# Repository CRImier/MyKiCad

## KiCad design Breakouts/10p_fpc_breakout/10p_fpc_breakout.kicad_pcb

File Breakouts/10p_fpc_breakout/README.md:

# 10-pin FPC/FFC breakout - 0.5/0.8/1mm

This is a simple breakout that exposes all pins of a 10-pin FFC connector.
You can do whatever with it.

On one side, there's footprints for 0.5mm and 0.8mm connectors.
On the other side, there's a footprint for 1mm connectors.

For instance, it should be quite usable for Sharp memory LCDs.
It will kinda sorta work for smaller-pin-count connectors too.

## Notes

- Pin headers are arranged in a way that this board can be plugged into a breadboard.

## Info

- Software: Kicad 6
- Version: 1
- PCB size: 9*20mm
- Layer count: 2

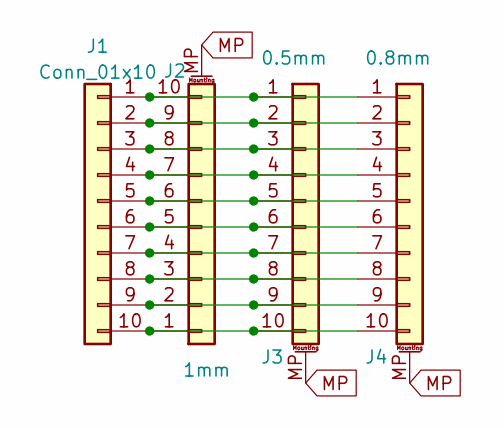
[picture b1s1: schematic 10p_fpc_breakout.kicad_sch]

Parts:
J1: Conn_01x10; PinHeader_1x10_P2.00mm_Vertical
J2: 1mm; FPC_10_10
J3: 0.5mm; FPC_10_05
J4: 0.8mm; FPC_10_08

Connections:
MP: J2.MP (MountPin), J3.MP (MountPin), J4.MP (MountPin)
unnamed: J1.1, J2.10, J3.1, J4.1
unnamed: J1.2, J2.9, J3.2, J4.2
unnamed: J1.3, J2.8, J3.3, J4.3
unnamed: J1.4, J2.7, J3.4, J4.4
unnamed: J1.5, J2.6, J3.5, J4.5
unnamed: J1.6, J2.5, J3.6, J4.6
unnamed: J1.7, J2.4, J3.7, J4.7
unnamed: J1.8, J2.3, J3.8, J4.8
unnamed: J1.9, J2.2, J3.9, J4.9
unnamed: J1.10, J2.1, J3.10, J4.10

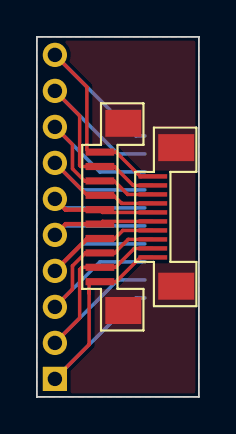
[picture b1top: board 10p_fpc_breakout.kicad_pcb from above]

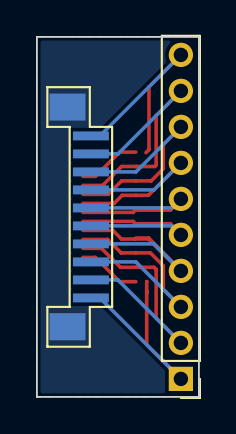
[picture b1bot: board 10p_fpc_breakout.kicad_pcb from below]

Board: 2 copper layers, 9.0 x 20.0 mm, 4 parts (2 on the bottom side), 11 nets.

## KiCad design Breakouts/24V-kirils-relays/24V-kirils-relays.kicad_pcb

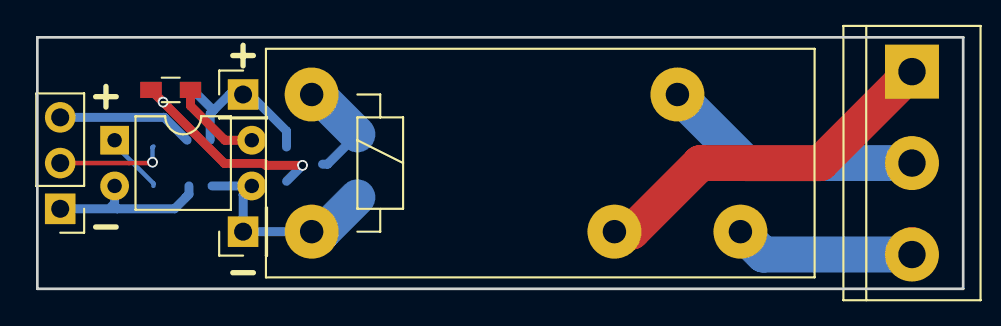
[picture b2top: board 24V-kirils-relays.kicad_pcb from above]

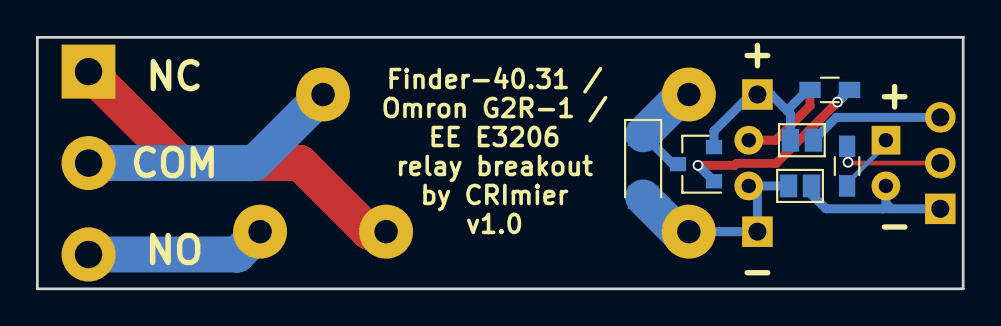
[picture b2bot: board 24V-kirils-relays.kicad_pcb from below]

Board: 2 copper layers, 51.4 x 14.0 mm, 13 parts (6 on the bottom side), 12 nets.

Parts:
D1: D_Small; D_MiniMELF
J1: Conn_01x03; Pin_Header_Straight_1x03_Pitch2.54mm
J2, J4: Conn_01x01; Pin_Header_Straight_1x01_Pitch2.54mm
J3: Conn_01x03; TerminalBlock_bornier-3_P5.08mm
JP1, JP2: Jumper; GS2
K1: FINDER-40.31; Relay_SPDT_Finder_40.31
Q1: Q_PNP_BEC; SOT-23
R1, R2, R3: 1k; R_0603_HandSoldering
U1: PC817; DIP-4_W7.62mm

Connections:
GND: J1.1, JP2.1, U1.2
unnamed: D1.1, K1.A1, Q1.3
unnamed: D1.2, J2.1, JP2.2, K1.A2, U1.3
unnamed: J1.2, R1.2
unnamed: J3.1, K1.12
unnamed: J3.2, K1.11
unnamed: J3.3, K1.14
unnamed: J4.1, JP1.2, Q1.2, R3.2
unnamed: Q1.1, R2.1, R3.1
unnamed: R1.1, U1.1
unnamed: R2.2, U1.4
VCC: J1.3, JP1.1

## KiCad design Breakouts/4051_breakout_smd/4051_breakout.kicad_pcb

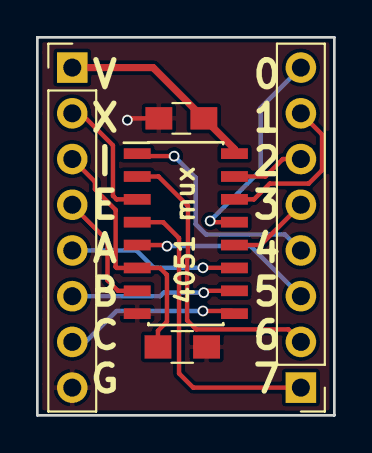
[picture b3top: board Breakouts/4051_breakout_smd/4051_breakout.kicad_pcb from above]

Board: 2 copper layers, 16.5 x 21.0 mm, 5 parts (0 on the bottom side), 16 nets.

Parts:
C1: C_Small; C_0805_HandSoldering
J1, J2: Conn_01x08; Pin_Header_Straight_1x08_Pitch2.54mm
R1: 10K; R_0805_HandSoldering
U2: 4051; SOIC-16_3.9x9.9mm_Pitch1.27mm

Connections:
A: J1.5, U2.11
B: J1.6, U2.10
C: J1.7, U2.9
E: J1.4, U2.7
I: J1.3, R1.1, U2.6
unnamed: J2.1, U2.4
unnamed: J2.2, U2.2
unnamed: J2.3, U2.5
unnamed: J2.4, U2.1
unnamed: J2.5, U2.12
unnamed: J2.6, U2.15
unnamed: J2.7, U2.14
unnamed: J2.8, U2.13
VDD: C1.1, J1.1, U2.16
VSS: C1.2, J1.8, R1.2, U2.8
X: J1.2, U2.3

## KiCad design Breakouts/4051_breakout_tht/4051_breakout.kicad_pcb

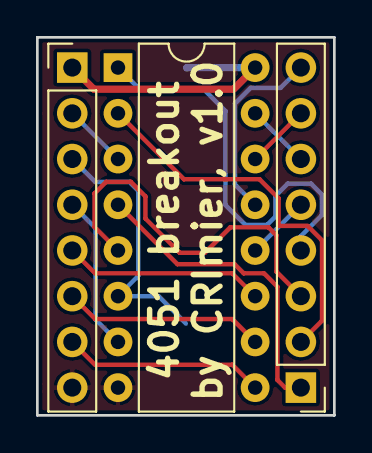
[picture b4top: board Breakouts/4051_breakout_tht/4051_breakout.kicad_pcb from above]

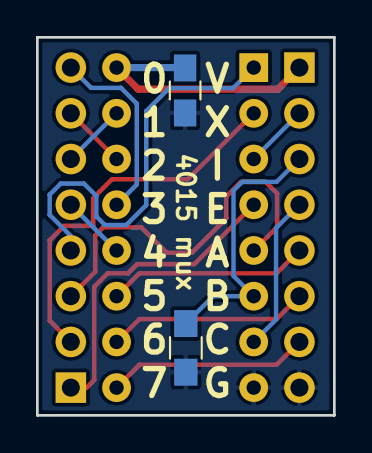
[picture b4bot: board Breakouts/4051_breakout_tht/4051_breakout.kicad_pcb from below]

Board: 2 copper layers, 16.5 x 21.0 mm, 5 parts (2 on the bottom side), 16 nets.

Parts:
C1: C_Small; C_0805_HandSoldering
J1, J2: Conn_01x08; Pin_Header_Straight_1x08_Pitch2.54mm
R1: 10K; R_0805_HandSoldering
U1: 4051; DIP-16_W7.62mm

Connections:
A: J1.5, U1.11
B: J1.6, U1.10
C: J1.7, U1.9
E: J1.4, U1.7
I: J1.3, R1.1, U1.6
unnamed: J2.1, U1.4
unnamed: J2.2, U1.2
unnamed: J2.3, U1.5
unnamed: J2.4, U1.1
unnamed: J2.5, U1.12
unnamed: J2.6, U1.15
unnamed: J2.7, U1.14
unnamed: J2.8, U1.13
VDD: C1.1, J1.1, U1.16
VSS: C1.2, J1.8, R1.2, U1.8
X: J1.2, U1.3
